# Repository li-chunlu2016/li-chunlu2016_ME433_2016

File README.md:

Li-Chun Lu
5/8/2016
This repository contains files for MECH433 Advanced Mechatronics.

Files will include homeworks and projects.

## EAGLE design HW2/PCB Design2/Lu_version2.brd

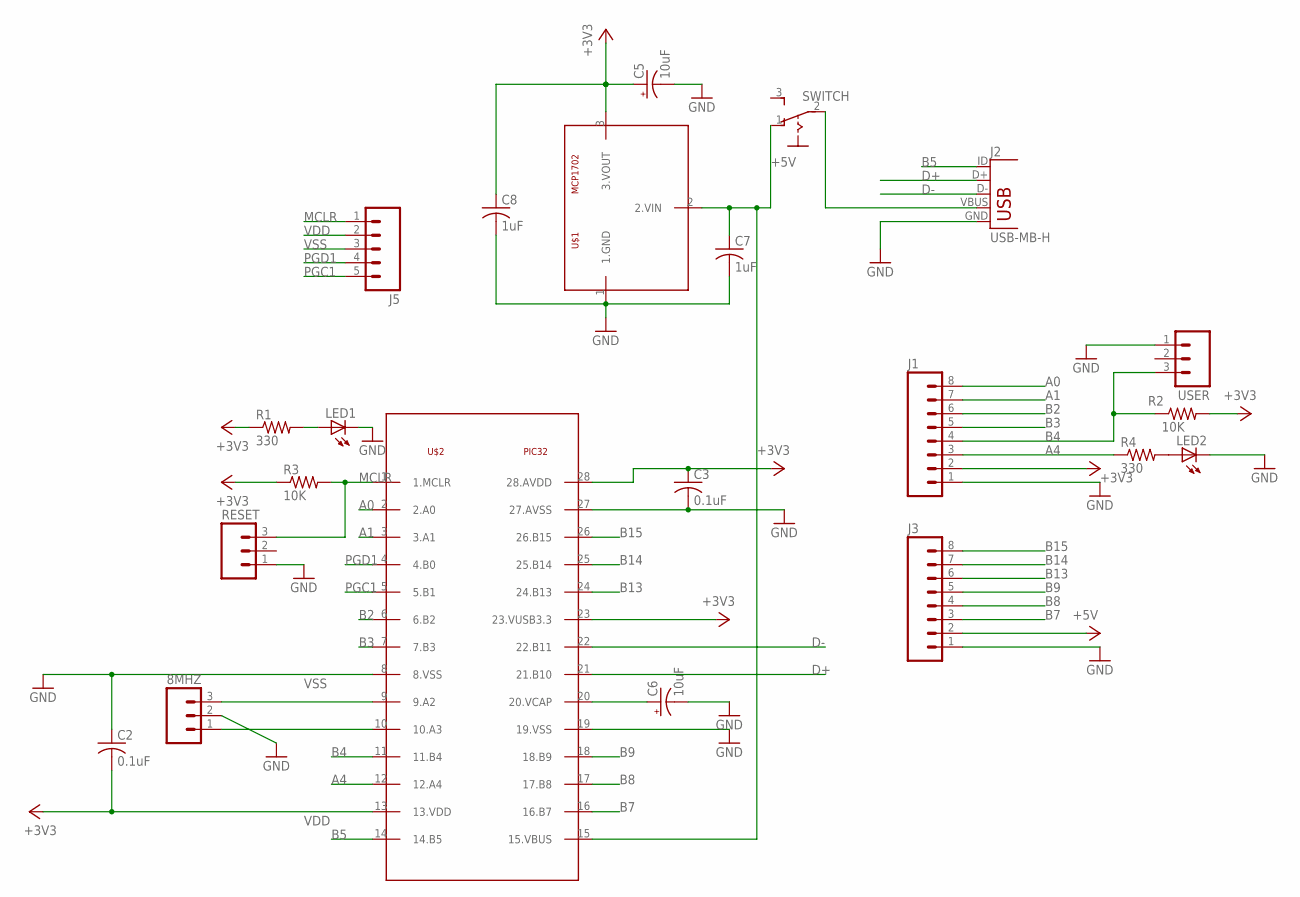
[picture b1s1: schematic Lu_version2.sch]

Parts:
8MHZ: M03PTH; 1X03
C2, C3: 0.1uF; C025-030X050
C5, C6: 10uF; B45181A
C7, C8: 1uF; C025-030X050
J1, J3: M08; 1X08_ROUND
J2: USB-MB-H
J5: M05PTH; 1X05
LED1, LED2: LED3MM
R1, R4: 330; 0207/10
R2, R3: 10K; 0207/10
RESET: M03PTH; 1X03
SWITCH: 255SB
U$1: MCP1702; TO92
U$2: PIC32; DIL28-3
USER: M03PTH; 1X03

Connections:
+3V3: C3.1, C5.+, C8.1, J1.2, R1.1, R2.2, R3.1, U$1.3 (3.VOUT), U$2.23 (23.VUSB3.3), U$2.28 (28.AVDD)
+5V: C7.1, J3.2, SWITCH.1 (O), U$1.2 (2.VIN), U$2.15 (15.VBUS)
A0: J1.8, U$2.2 (2.A0)
A1: J1.7, U$2.3 (3.A1)
A4: J1.3, R4.1, U$2.12 (12.A4)
B2: J1.6, U$2.6 (6.B2)
B3: J1.5, U$2.7 (7.B3)
B4: J1.4, R2.1, U$2.11 (11.B4), USER.3
B5: J2.ID, U$2.14 (14.B5)
B7: J3.3, U$2.16 (16.B7)
B8: J3.4, U$2.17 (17.B8)
B9: J3.5, U$2.18 (18.B9)
B13: J3.6, U$2.24 (24.B13)
B14: J3.7, U$2.25 (25.B14)
B15: J3.8, U$2.26 (26.B15)
D+: J2.D+, U$2.21 (21.B10)
D-: J2.D-, U$2.22 (22.B11)
GND: 8MHZ.2, C3.2, C5.-, C6.-, C7.2, C8.2, J1.1, J2.GND, J3.1, LED1.K (C), LED2.K (C), RESET.1, U$1.1 (1.GND), U$2.19 (19.VSS), U$2.27 (27.AVSS), USER.1
MCLR: J5.1, R3.2, RESET.3, U$2.1 (1.MCLR)
unnamed: J2.VBUS, SWITCH.2
unnamed: LED1.A, R1.2
unnamed: 8MHZ.3, U$2.9 (9.A2)
unnamed: LED2.A, R4.2
unnamed: 8MHZ.1, U$2.10 (10.A3)
unnamed: C6.+, U$2.20 (20.VCAP)
PGC1: J5.5, U$2.5 (5.B1)
PGD1: J5.4, U$2.4 (4.B0)
VDD: C2.2, J5.2, U$2.13 (13.VDD)
VSS: C2.1, J5.3, U$2.8 (8.VSS)

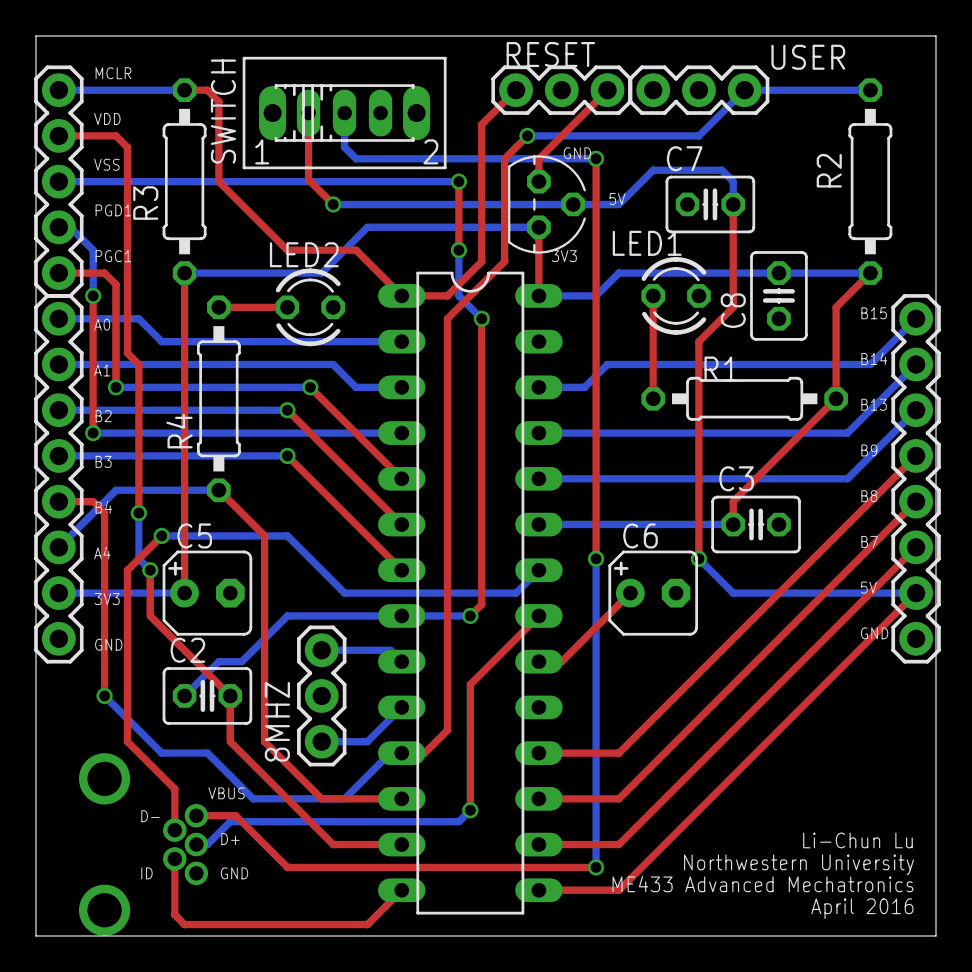
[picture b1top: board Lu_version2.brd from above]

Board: 2 copper layers, 50.0 x 50.0 mm, 22 parts (0 on the bottom side), 29 nets.

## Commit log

2016-03-31 My first commit
2016-03-31 My second commit
2016-03-31 My third commit
2016-03-31 Folder for HW1
2016-04-03 write up for HW1
2016-04-03 edit
2016-04-03 circuit diagram and Nscope screen shots
2016-04-03 main code
2016-04-03 code edit
2016-04-04 edit
    new homework1 folder
2016-04-04 final code
2016-04-04 final comment on hw1 folder
    check hw1b.X
2016-04-06 create hw2 folder
2016-04-06 create project on EAGLE
2016-04-11 error check
2016-04-14 Ready to be checked before order
2016-04-16 create files for hw4
2016-04-20 HW4 SPI plots
    10Hz sine wave
    5Hz triangle wave
2016-04-21 working final code
2016-04-21 push button (GP7) to lit LED (GP0)
2016-04-25 new folder for IMU hw6
2016-04-26 working code
2016-04-26 add screenshot for the working code
2016-04-26 just cleaning up the folds and file, all working code remain the same.
2016-04-26 this is for testing
2016-04-26 test jinxing code
2016-05-06 new folder for HW5 TFT LCD
2016-05-06 edit
    need to covert short to int to display IMU values
2016-05-06 working code for TFTLCD hw5
2016-05-12 working sliding bar
2016-05-18 wheel hub design
2016-05-25 wheel hub 3D printed
2016-06-03 camera app and slide bar to control threshold value
2016-06-05 Android app that mixes the camera and CDC apps together.
2016-06-05 slide bar and qq work now
2016-06-05 working code
    pic can read slide bar value and change the LED brightness.
2016-06-06 working code for robot car
2016-06-06 final pic code for robot car
2016-06-07 result submit
2016-06-21 upload
2016-06-29 Sort Texture first upload
2016-06-29 remove
2016-08-01 test image
2016-08-01 test images
2016-08-02 test
2016-08-03 change images
2016-08-10 new omg
